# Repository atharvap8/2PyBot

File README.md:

# 2PyBot: Self-Balancing Robot

2PyBot v4.0.1 is an ESP32 self-balancing robot with two M0601 RS485 BLDC hub motors, integrated wheel feedback, and an ISM6HG256X IMU. The firmware uses **LQR/LQI state feedback** for balance and position hold. An EVOFOX One S gamepad pairs directly through Bluepad32. USB serial carries host drive commands, telemetry, and parameter tuning. See the [BLDC integration notes](docs/BLDC_V4.md) for wiring, polarity, full-stick control and turning changes.

## Current firmware

- 200 Hz control loop using pitch, pitch rate, wheel position, velocity, and position integral.
- One RS485 UART per wheel, with current control and absolute-position feedback.
- Encoder-differential heading hold and slew-limited steering.
- Normal hold, stiff hold, velocity tracking, and climb reference tracking.
- Terrain roughness, airborne, and landing detection with pitch-gain softening.
- Metadata-driven runtime parameters with bounded writes and separate BLDC NVS storage.
- Auto-tuning routines for wobble, trim, radius, and stall speed, with current limitations documented in the tuning guide.
- WS2812 status ring, camera pan/zoom servos, and PWM torch.

## Control and communication

The gamepad's left stick drives and steers. The right stick pans and zooms the camera. START requests arming; SELECT stops balancing. LB toggles LOW/HIGH speed, RB toggles the torch, and the D-pad controls hold modes and torch brightness.

Fresh host `V,<forward>,<steering>,<enable>` commands take priority over gamepad driving. `V` commands do not arm the robot. Use gamepad START or serial `E`. With no fresh input, drive commands become zero and balancing continues.

USB serial runs at **460800 baud**. The firmware emits `O` odometry and `D` debug telemetry at nominal 50 Hz, plus `HM` motor feedback at 10 Hz. Debug starts enabled; `L` toggles it. See the [serial protocol](firmware/BaseLink/PROTOCOL.md) for fields and commands.

## Repository layout

```text
firmware/
  BaseLink/                 Robot firmware and serial protocol
    BaseLink.ino            State machine, control, input arbitration
    config.h                Pins and compiled defaults
    params.h / params.cpp   Runtime parameters and NVS persistence
    autotune.h              Calibration and tuning routines
    terrain.h               Roughness, airborne, and landing detection
    bt_gamepad.h            Bluepad32 input mapping
    imu_sensor.h / .cpp      Mahony attitude estimation
    m0601.h / .cpp           RS485 framing, CRC and reply ownership
    hub_drive.h / .cpp       Two hub motors, feedback and mode handshake
    hub_control.h           Balance-priority common/turn current control
    led_ring.h / .cpp        WS2812 status display
    payload.h               Camera servos and torch
  Controller/               Legacy ESP-NOW joystick transmitter
software/
  android/                  Kotlin/Compose Android app
  radxa/
    console/                Current browser console and Android API
    deployment/             Installed services, MediaMTX, and device rules
  runtime/vision_controller/ Older collision guard and person follower
gui/                        Legacy PID desktop interface
tools/
  controller_lab/           Browser simulation lab
  tuner/                    Legacy Web Serial PID tuner
docs/                       Architecture, control theory, tuning, history
scripts/                    Model generation and Radxa utilities
hardware/cad/enclosure/rev5/ OpenSCAD enclosure source and STL exports
models/                     CAD assets
assets/                     Project media
```

## Build and first connection

1. Install the ESP32 + Bluepad32 board package and the libraries listed in the [firmware setup guide](firmware/BaseLink/README.md).
2. Select ESP32 Dev Module with the Huge APP partition scheme.
3. Open `firmware/BaseLink/BaseLink.ino`, review the pin assignments in `config.h`, and flash.
4. Open USB serial at 460800 baud with newline termination. Check the IMU and driver boot messages, then send `P?` to inspect loaded parameters.
5. Pair the EVOFOX One S in Home+A mode. Leave both sticks centered while calibration completes.
6. Use the [v4 hardware guide](docs/BLDC_V4.md) for the BLDC pin map, confirmed polarity, parameter schema and offline verification.

Saved v4 NVS parameters take precedence over compiled defaults in `2pybot-bldc4`. `PD` restores defaults in RAM; `PS` saves them with motors stopped. `ISGN` and `RPMSGN` are fixed at -1; `HUBVSRC` defaults to 1. Full-stick HIGH requests 1.00 m/s; `MAXSPD=0` leaves firmware speed uncapped. `VNOLOAD` is informational, not a driving limit.

## Host software status

| Component | Current compatibility |
| :--- | :--- |
| USB terminal or custom serial client | Supports the current parameter and telemetry protocol |
| `software/radxa/console/` | Current Radxa console: 460800 baud, live parameter metadata, browser UI, Android API, and WebRTC camera |
| `software/android/` | Kotlin/Compose client for console HTTP/WebSocket and MediaMTX WHEP; parameter groups are dynamic |
| `software/runtime/vision_controller/radxa_brain.py` | Uses `O` and `V` messages, but still has 115200 baud and 0.035 m radius constants; align both before use |
| `gui/robot_controller_ui.py` | Legacy PID UI: 115200 baud, tab-separated telemetry, and `$` commands; needs a protocol update |
| `tools/tuner/tuner.html` | Legacy Web Serial PID tuner; not a current parameter-store client |
| `firmware/Controller/Controller.ino` | Legacy ESP-NOW transmitter; current BaseLink has no ESP-NOW receiver |

The current console package was imported from the Cubie A7A. See its [setup and API guide](software/radxa/console/README.md) and [deployment layout](software/radxa/README.md). Its debug parser reads the 20 controller/terrain fields plus nine appended fall-prevention fields; a terrain parameter tab remains pending. **Driving view** shows the assembled CAD, measured VL53L5CX returns, trail and optional forward-reference guard, off by default. Live camera is available separately in that view and in Camera.

Local revision **3.9.0** adds a [predictive fall-prevention reference governor](docs/diagnostics/fall-prevention.md) with full recovery feedback and balance-priority steering allocation. Its read-only monitor is `/ui/drive-monitor.html`; a repeat physical reversal test is needed to measure fall reduction.
Local revision **3.10.0** adds [automatic load-aware climb](docs/diagnostics/auto-climb.md), gradual controller handover and a fix for mild-recovery integral washout. Automatic/manual controls are at `/ui/auto-climb.html`; the recorder includes actual climb-integral and detector state.
Current development revision **4.0.0** replaces the stepper drive with [M0601 BLDC hubs](docs/BLDC_V4.md). It retains the [adaptive Android cockpit](docs/ANDROID_COCKPIT_DESIGN.md) and [route autopilot](docs/ROUTE_AUTOPILOT.md). [Compiled-build reflashing](docs/FIRMWARE_REFLASH.md) is under **More → Setup → Controller firmware**; its tuning-restore path requires a matching hardware schema. [Camera stabilisation](docs/CAMERA_STABILISATION.md) covers the proposed pitch gimbal and isolated sensor pod.

[Boot coordination](scripts/radxa/BOOT_COORDINATION.md) holds the ESP32's USB reset until the Radxa camera, API and hotspot are ready, then releases a firmware startup interlock. A deliberate local START request is still required. [Printed mass and LQI calculations](hardware/dynamics/README.md) contain re-sliced estimates and updated estimated gains validated against geometry, filtering, latency and acceleration limits.

The older Radxa brain provides GUARD/FOLLOW modes. It owns the camera and serial port, so it cannot run alongside the console. See its [setup guide](software/runtime/vision_controller/README_RADXA.md).

The [Android app](software/android/README.md) has Drive, Live, Map, Tune, Auto, Camera, Data and Setup screens. It defaults to the Radxa hotspot address `10.42.0.1`. Drive uses a touch-navigable shaded world; Data records labelled terrain sessions; Map and Setup export reports. Its Tune screen includes all groups reported by firmware, including TERRAIN. See [terrain sessions and Drive](docs/terrain-sessions.md) for current behaviour.

## Next vision milestones

The [Objects viewer and SLAM notes](docs/ML_AND_SLAM.md) describe the lightweight
ONNX detector, temporary tracks, and the calibration/telemetry needed for later mapping.

The [guided camera calibration suite](docs/CAMERA_CALIBRATION.md) provides
target printing, automatic capture/analysis and corrected previews, with depth
health and frame timing. It is available in the console's Calibration tab and
Android Camera screen. Real target views are needed to obtain actual coefficients.

The [vision roadmap](docs/VISION_ROADMAP.md) tracks camera distortion/intrinsic
calibration, sensor extrinsics, synchronized camera/ToF distance overlays and
later ONNX detection/tracking. Camera geometric calibration is separate from
the existing colour/exposure tuning. The first proposed milestone is a measured
intrinsic calibration and validated undistorted preview.

## Revision Table

The [Revision Table](docs/REVISION_HISTORY.md) covers the main releases and
features, along with estimated dates for upcoming work. Smaller fixes are grouped
together. See the [vision roadmap](docs/VISION_ROADMAP.md) for the detailed task list.

## Updating the bot

See the [one-pull development SOP](docs/DEVELOPMENT_SOP.md) for coordinated Git
pulls, versioned host releases, firmware updates and deployment LED states.

The managed source checkout is `/home/radxa/projects/2PyBot`; the console runs from a versioned release snapshot. After one-time setup, `git pull --ff-only` waits for coordinated deployment and reports its outcome. Firmware updates use the existing application-only flash worker when their inputs change. CAD/documentation-only updates leave running services untouched. See the SOP for setup, status and recovery, or [repo-based deployment](scripts/radxa/README.md) for legacy installations.

## Hardware defaults

| Component | Configuration |
| :--- | :--- |
| Robot controller | ESP32 DevKit |
| Wheel drive | Two M0601 BLDC hubs, independent RS485 UARTs, current mode |
| Wheel feedback | Integrated absolute position; internal 4096-count/revolution units |
| Wheel radius | 0.052 m compiled default |
| Attitude | ISM6HG256X accelerometer/gyro, Mahony filter |
| Compass | QMC5883L, tilt-compensated yaw telemetry |
| Gamepad | EVOFOX One S through Bluepad32 |
| Status ring | 16 WS2812 LEDs on GPIO 15 |
| Camera payload | MG90S pan/zoom servos on GPIO 26/0; torch on GPIO 2 |

## Enclosure CAD

[Revision 5](hardware/cad/enclosure/rev5/README.md) includes the base tray, shell, face plate, and left/right motor covers as OpenSCAD source and five STL exports. The enclosure is **not yet printed or physically fit-tested**. Estimated dimensions are marked in the source. The imported face STL has three zero-area triangles that need re-export or repair before printing.

The existing simplified STEP model remains in `models/2pybot_simplified.step`; it is separate from the revision-5 enclosure package.

## Documentation

| Document | Contents |
| :--- | :--- |
| [Firmware setup](firmware/BaseLink/README.md) | Build, wiring, pairing, controls |
| [Serial protocol](firmware/BaseLink/PROTOCOL.md) | Commands, parameter records, telemetry fields |
| [Radxa console](software/radxa/console/README.md) | Browser UI, Android API, camera pipeline, deployment |
| [Lidar mapping](docs/LIDAR_SLAM.md) | RPLIDAR C1 wiring, standalone SLAM page, first use |
| [Android app](software/android/README.md) | Build, host connection, screens, parameter and video transport |
| [Vision roadmap](docs/VISION_ROADMAP.md) | Planned lens calibration, sensor geometry, depth fusion and ONNX perception |
| [Camera calibration](docs/CAMERA_CALIBRATION.md) | Guided capture, lens fitting, reports, depth health and frame timing |
| [Terrain sessions and Drive](docs/terrain-sessions.md) | Recording, 3D world coordinates, guard and range calibration |
| [Radxa deployment](scripts/radxa/README.md) | Git updates, selective restarts, systemd timer, health checks |
| [Enclosure CAD](hardware/cad/enclosure/rev5/README.md) | Revision-5 source, exports, dimensions, and current print status |
| [System architecture](docs/BaseLink/System_Architecture.md) | Sensors, control, actuation, host links |
| [LQR/LQI theory](docs/BaseLink/PID_Theory_and_Math.md) | State feedback, control modes, filtering, limits |
| [Configuration and tuning](docs/BaseLink/Config_and_Tuning_Guide.md) | Defaults, runtime settings, calibration |
| [Program flow](docs/BaseLink/Program_Flow_State_Machine.md) | Boot sequence and state transitions |
| [Troubleshooting](docs/BaseLink/Troubleshooting_Guide.md) | Common faults and source-level checks |
| [Detailed reference](docs/BaseLink/100+_WHAT_AND_HOWS.md) | 126 code-mapped checks |
| [TMC2226 migration](docs/BaseLink/TMC2226_Migration.md) | Driver configuration and migration history |
| [Project history](docs/BaseLink/Project_History.md) | PID, ESP-NOW, LQR/LQI, and runtime-tuning milestones |
| [Legacy transmitter](docs/Controller/System_Architecture.md) | ESP-NOW joystick packet and sampling |

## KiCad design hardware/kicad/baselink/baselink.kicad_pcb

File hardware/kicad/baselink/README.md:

# BaseLink controller board (KiCad 10)

STM32G474RET6 balance controller for 2PyBot: ELRS radio (CRSF), two RS485
hub-motor links, Radxa Cubie host header, 5S battery input with ideal-diode
reverse protection and current monitor, an LM5069 hot-swap motor bus switch
driven by a hardware safety chain (motor watchdog AND E-stop), three
independent 5 V rails and a 3V3 LDO. Architecture: see the conversation
notes / `docs` (STM32 + ELRS plan).

**Status: schematic draft r0.1 + placeholder PCB.** Footprints are placed
automatically in one region per block; nothing is routed. Verify the STM32 pin
map in STM32CubeMX, the Cubie A7A 40-pin mapping, the ISM6HG256X pinout
(ISM330DHCX symbol used) and the hot-swap/UVLO values before layout.

## Files

| File | What |
|---|---|
| `baselink.kicad_pro` | Project: net classes (Default, Battery, Rail5V, RS485), 4-layer rules |
| `baselink.kicad_sch` | Root: block diagram of the hierarchical sheets |
| `power_input`, `motor_power`, `regulators`, `mcu`, `rs485`, `comms`, `io` `.kicad_sch` | One sheet per block |
| `baselink.kicad_pcb` | Placeholder board: all 144 footprints, nets, outline, M3 holes, GND plane on In1 |
| `baselink.kicad_sym`, `sym-lib-table` | Project power symbols (VBAT, VMOT, +5V_SBC, +5V_ACT, +5V_CTRL, +3V3A) |
| `build/baselink_schematic.pdf` | Schematic PDF |
| `build/erc.rpt`, `build/drc.rpt` | Last check results |
| `tools/design.py` | **The circuit**: every part, footprint and pin-to-net map |
| `tools/gen_sch.py` | Generates the project, symbol library and all sheets |
| `tools/gen_pcb.py` | Generates the board with KiCad's Python (pcbnew) |

## Regenerate

```powershell
cd hardware\kicad\baselink
python tools\gen_sch.py                                  # project + schematic + build\netlist.json
D:\7_Tools\KiCad\bin\python.exe tools\gen_pcb.py         # placeholder board
D:\7_Tools\KiCad\bin\kicad-cli.exe sch erc baselink.kicad_sch -o build\erc.rpt --severity-all
D:\7_Tools\KiCad\bin\kicad-cli.exe pcb drc baselink.kicad_pcb -o build\drc.rpt --severity-all
D:\7_Tools\KiCad\bin\kicad-cli.exe sch export pdf baselink.kicad_sch -o build\baselink_schematic.pdf
```

Edit `tools/design.py`, not the generated `.kicad_sch` files. `gen_sch.py`
checks every pin name against the library symbol and every pin number against
the footprint's pads, and lists unconnected pins.

**Once layout starts, stop regenerating the board.** Edit the schematic source
and use *Tools → Update PCB from Schematic* in KiCad; footprints carry their
schematic links, so placement and routing are kept.

## Known check results

- ERC: 1 warning. IMU `SDx` is tied to GND as the datasheet recommends for an
  unused aux bus; it is bidirectional, so ERC flags it against the GND flag.
- DRC: only unrouted connections and library silkscreen overlaps.

## Sheets

| Sheet | Contents |
|---|---|
| Power input | XT60, 30 A blade fuse, LM74700 + N-FET ideal diode, SMDJ26A, bulk, 1 mΩ shunt + INA228, VBAT ADC divider |
| Motor switch | LM5069 hot-swap + N-FET + 2 mΩ sense, fail-safe UVLO enable (BSS138 + BSS84), 74LVC1G123 motor watchdog, 74LVC1G08 AND with the E-stop loop, VMOT TVS + bulk, 2× XT30 |
| Regulators | 3× Pololu D36V step-down placeholders (+5V_SBC 5 A, +5V_ACT 3 A, +5V_CTRL 0.6 A), TLV75733 3V3 LDO, power LED |
| MCU | STM32G474RET6 LQFP64, decoupling, VDDA ferrite, 24 MHz crystal, BOOT0/NRST, buttons, 10-pin SWD, USB-C with USBLC6 and VBUS OR-ing, status LED |
| RS485 | 2× socketed DIP-8 transceivers (SN65HVD3082E class), termination jumpers, DNP bias, SM712, JST-GH |
| Comms | ELRS JST-GH, Radxa 2×20 socket (5 V, host UART, BOOT0/NRST via 1 k, lidar and ToF pass-through), SN65HVD230 CAN, spare UART |
| IO | IMU (SPI + 2 INT), 2× Qwiic, WS2812 level shifter + connector, 4 servo headers, torch MOSFET, buzzer driver, rail and NTC ADC dividers |

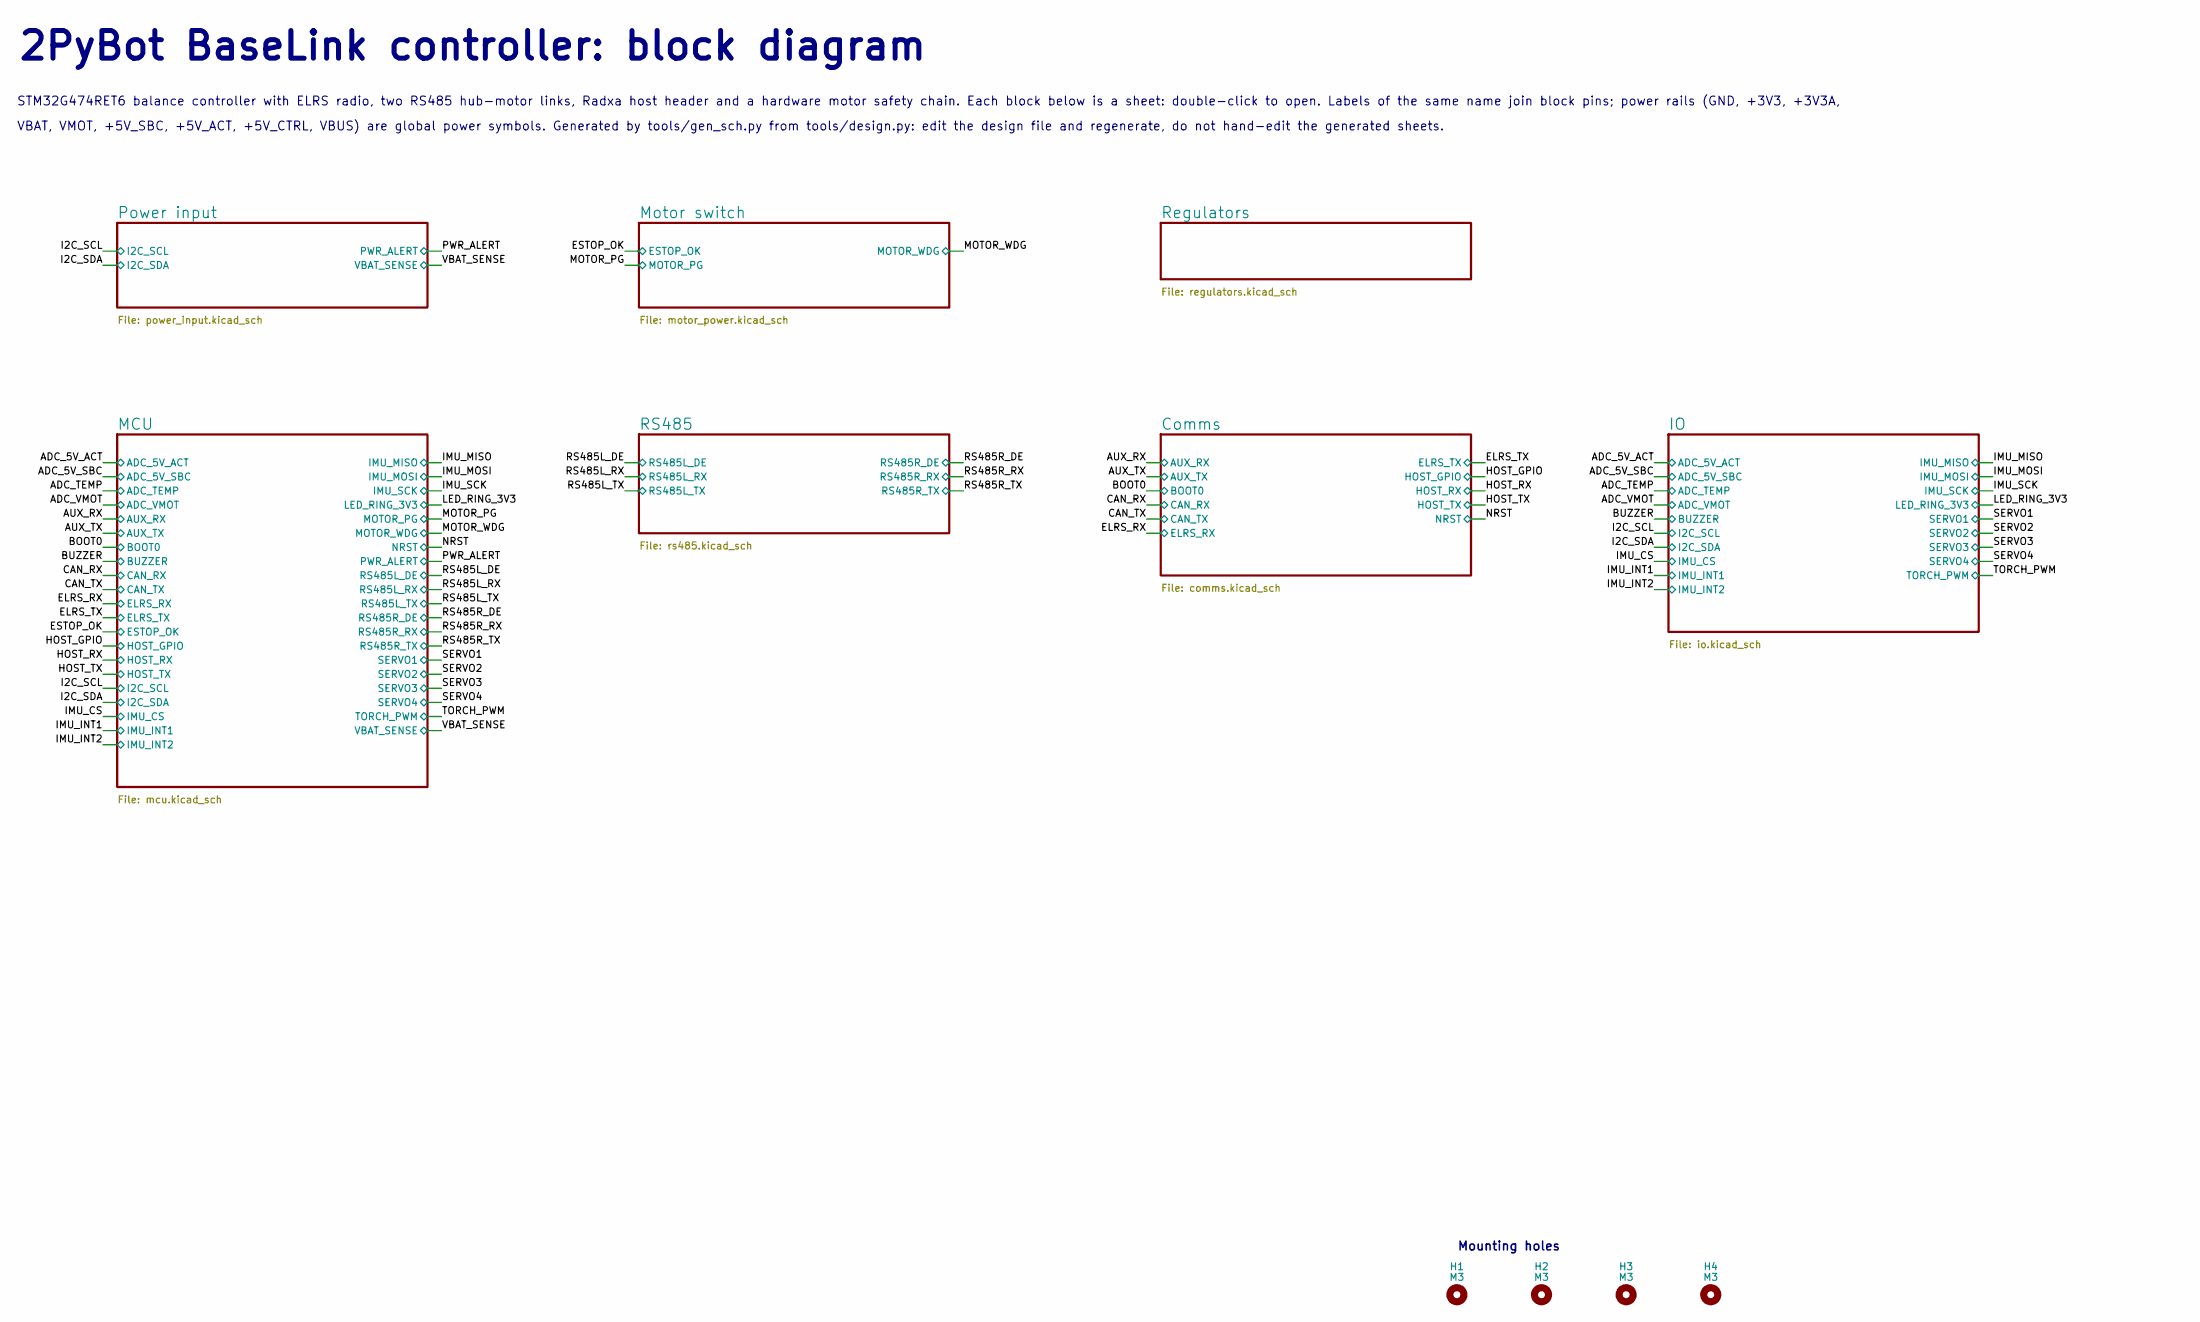
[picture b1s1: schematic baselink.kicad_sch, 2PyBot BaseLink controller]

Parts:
H1, H2, H3, H4: M3; MountingHole_3.2mm_M3

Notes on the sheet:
2PyBot BaseLink controller: block diagram
STM32G474RET6 balance controller with ELRS radio, two RS485 hub-motor links, Radxa host header and a hardware motor safety chain. Each block below is a sheet: double-click to open. Labels of the same name join block pins; power rails (GND, +3V3, +3V3A,
VBAT, VMOT, +5V_SBC, +5V_ACT, +5V_CTRL, VBUS) are global power symbols. Generated by tools/gen_sch.py from tools/design.py: edit the design file and regenerate, do not hand-edit the generated sheets.
Mounting holes

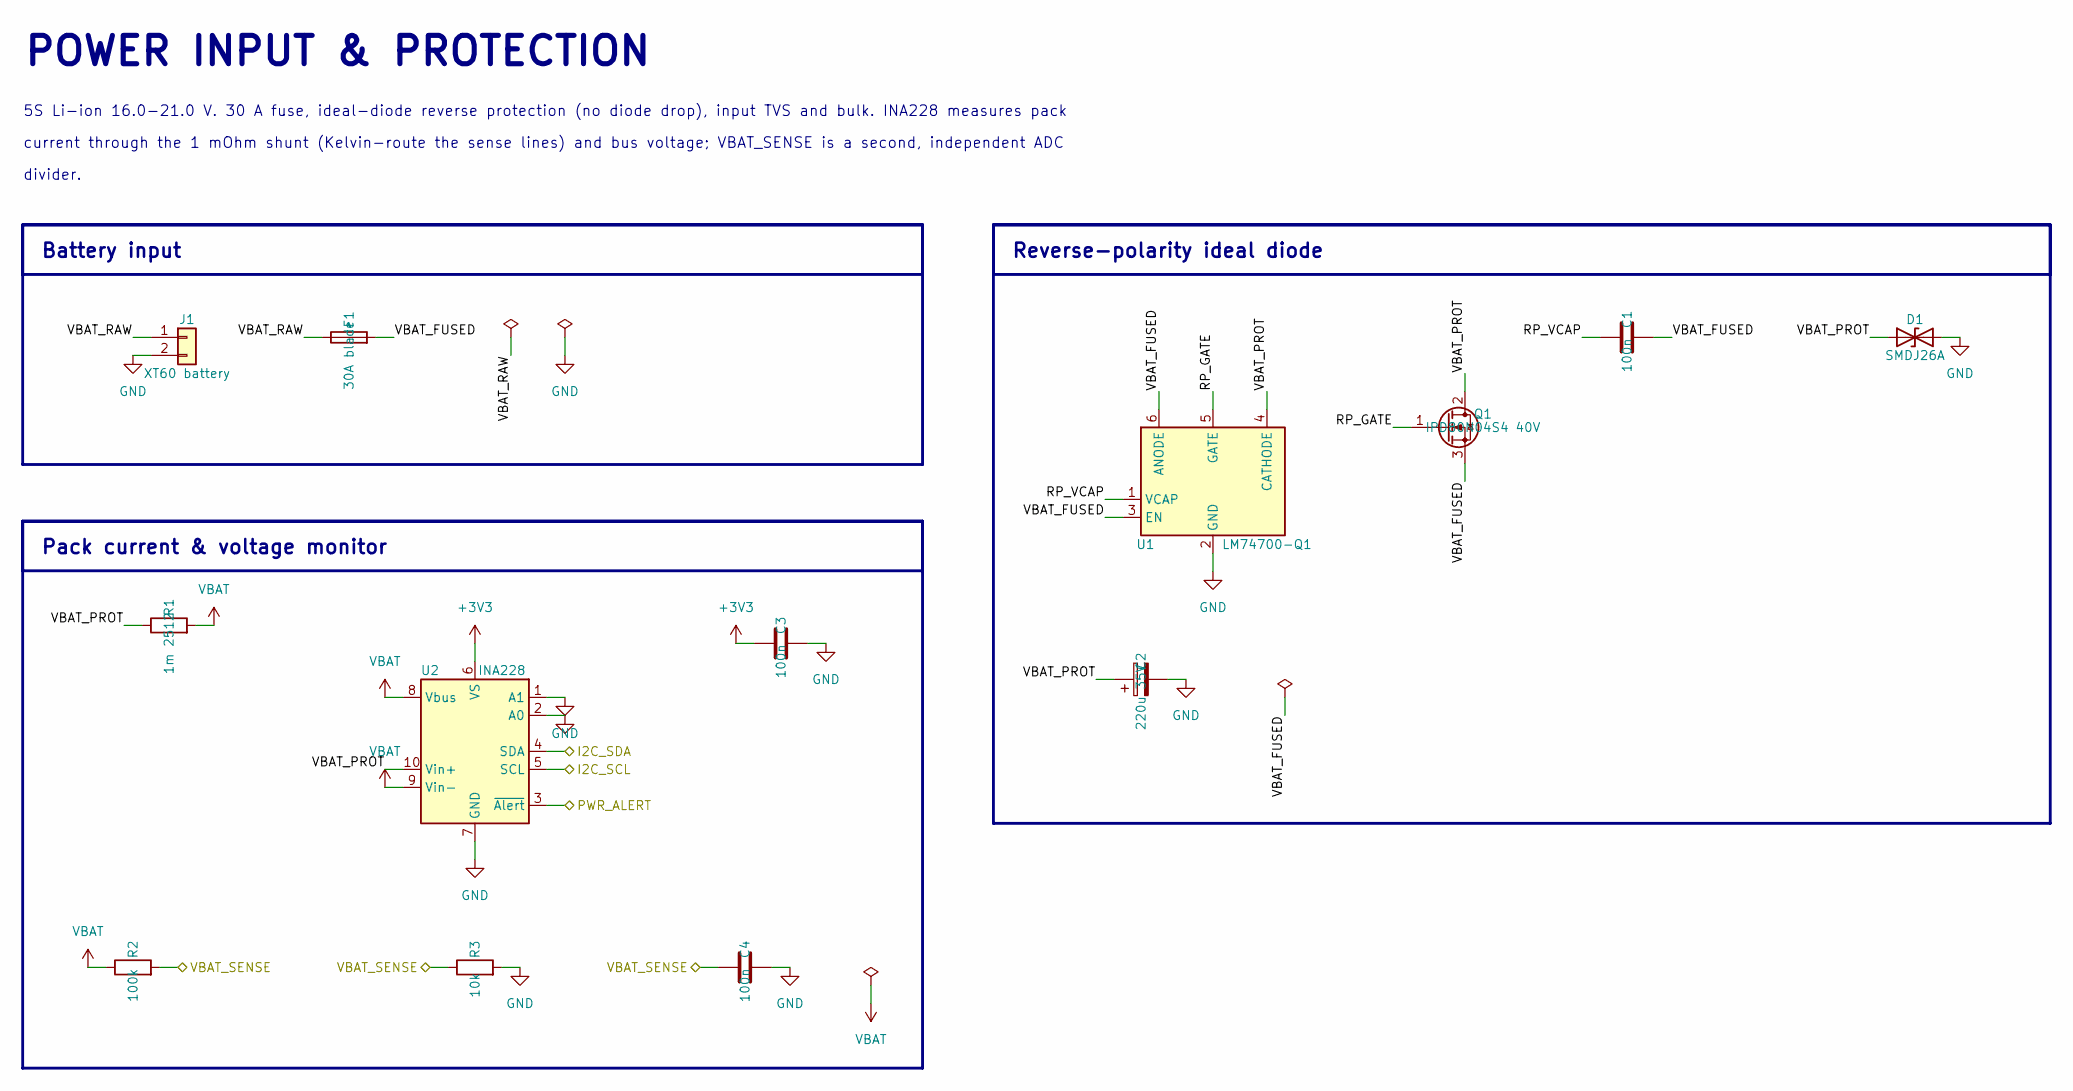
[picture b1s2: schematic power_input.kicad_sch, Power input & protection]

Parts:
C1, C3, C4: 100n; C_0603_1608Metric
C2: 220u 35V; CP_Elec_10x10
D1: SMDJ26A; D_SMC
F1: 30A blade; Fuseholder_Blade_Mini_Keystone_3568
J1: XT60 battery; AMASS_XT60PW-M_1x02_P7.20mm_Horizontal
Q1: IPD80N04S4 40V; TO-252-2
R1: 1m 2512; R_2512_6332Metric
R2: 100k; R_0603_1608Metric
R3: 10k; R_0603_1608Metric
U1: LM74700-Q1; SOT-23-6
U2: INA228; TSSOP-10_3x3mm_P0.5mm

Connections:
+3V3: C3.1, U2.6 (VS); also elsewhere on the board
/I2C_SCL: U2.5 (SCL); also elsewhere on the board
/I2C_SDA: U2.4 (SDA); also elsewhere on the board
/PWR_ALERT: U2.3 (~Alert); also elsewhere on the board
/Power input/RP_GATE: Q1.1 (G), U1.5 (GATE)
/Power input/RP_VCAP: C1.1, U1.1 (VCAP)
/Power input/VBAT_FUSED: C1.2, F1.2, Q1.3 (S), U1.3 (EN), U1.6 (ANODE)
/Power input/VBAT_PROT: C2.1, D1.1 (A1), Q1.2 (D), R1.1, U1.4 (CATHODE), U2.10 (Vin+)
/Power input/VBAT_RAW: F1.1, J1.1
/VBAT_SENSE: C4.1, R2.2, R3.1; also elsewhere on the board
GND: C2.2, C3.2, C4.2, D1.2 (A2), J1.2, R3.2, U1.2 (GND), U2.1 (A1), U2.2 (A0), U2.7 (GND); also elsewhere on the board
VBAT: R1.2, R2.1, U2.8 (Vbus), U2.9 (Vin-); also elsewhere on the board

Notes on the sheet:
POWER INPUT & PROTECTION
5S Li-ion 16.0-21.0 V. 30 A fuse, ideal-diode reverse protection (no diode drop), input TVS and bulk. INA228 measures pack
current through the 1 mOhm shunt (Kelvin-route the sense lines) and bus voltage; VBAT_SENSE is a second, independent ADC
divider.
Battery input
Reverse-polarity ideal diode
Pack current & voltage monitor

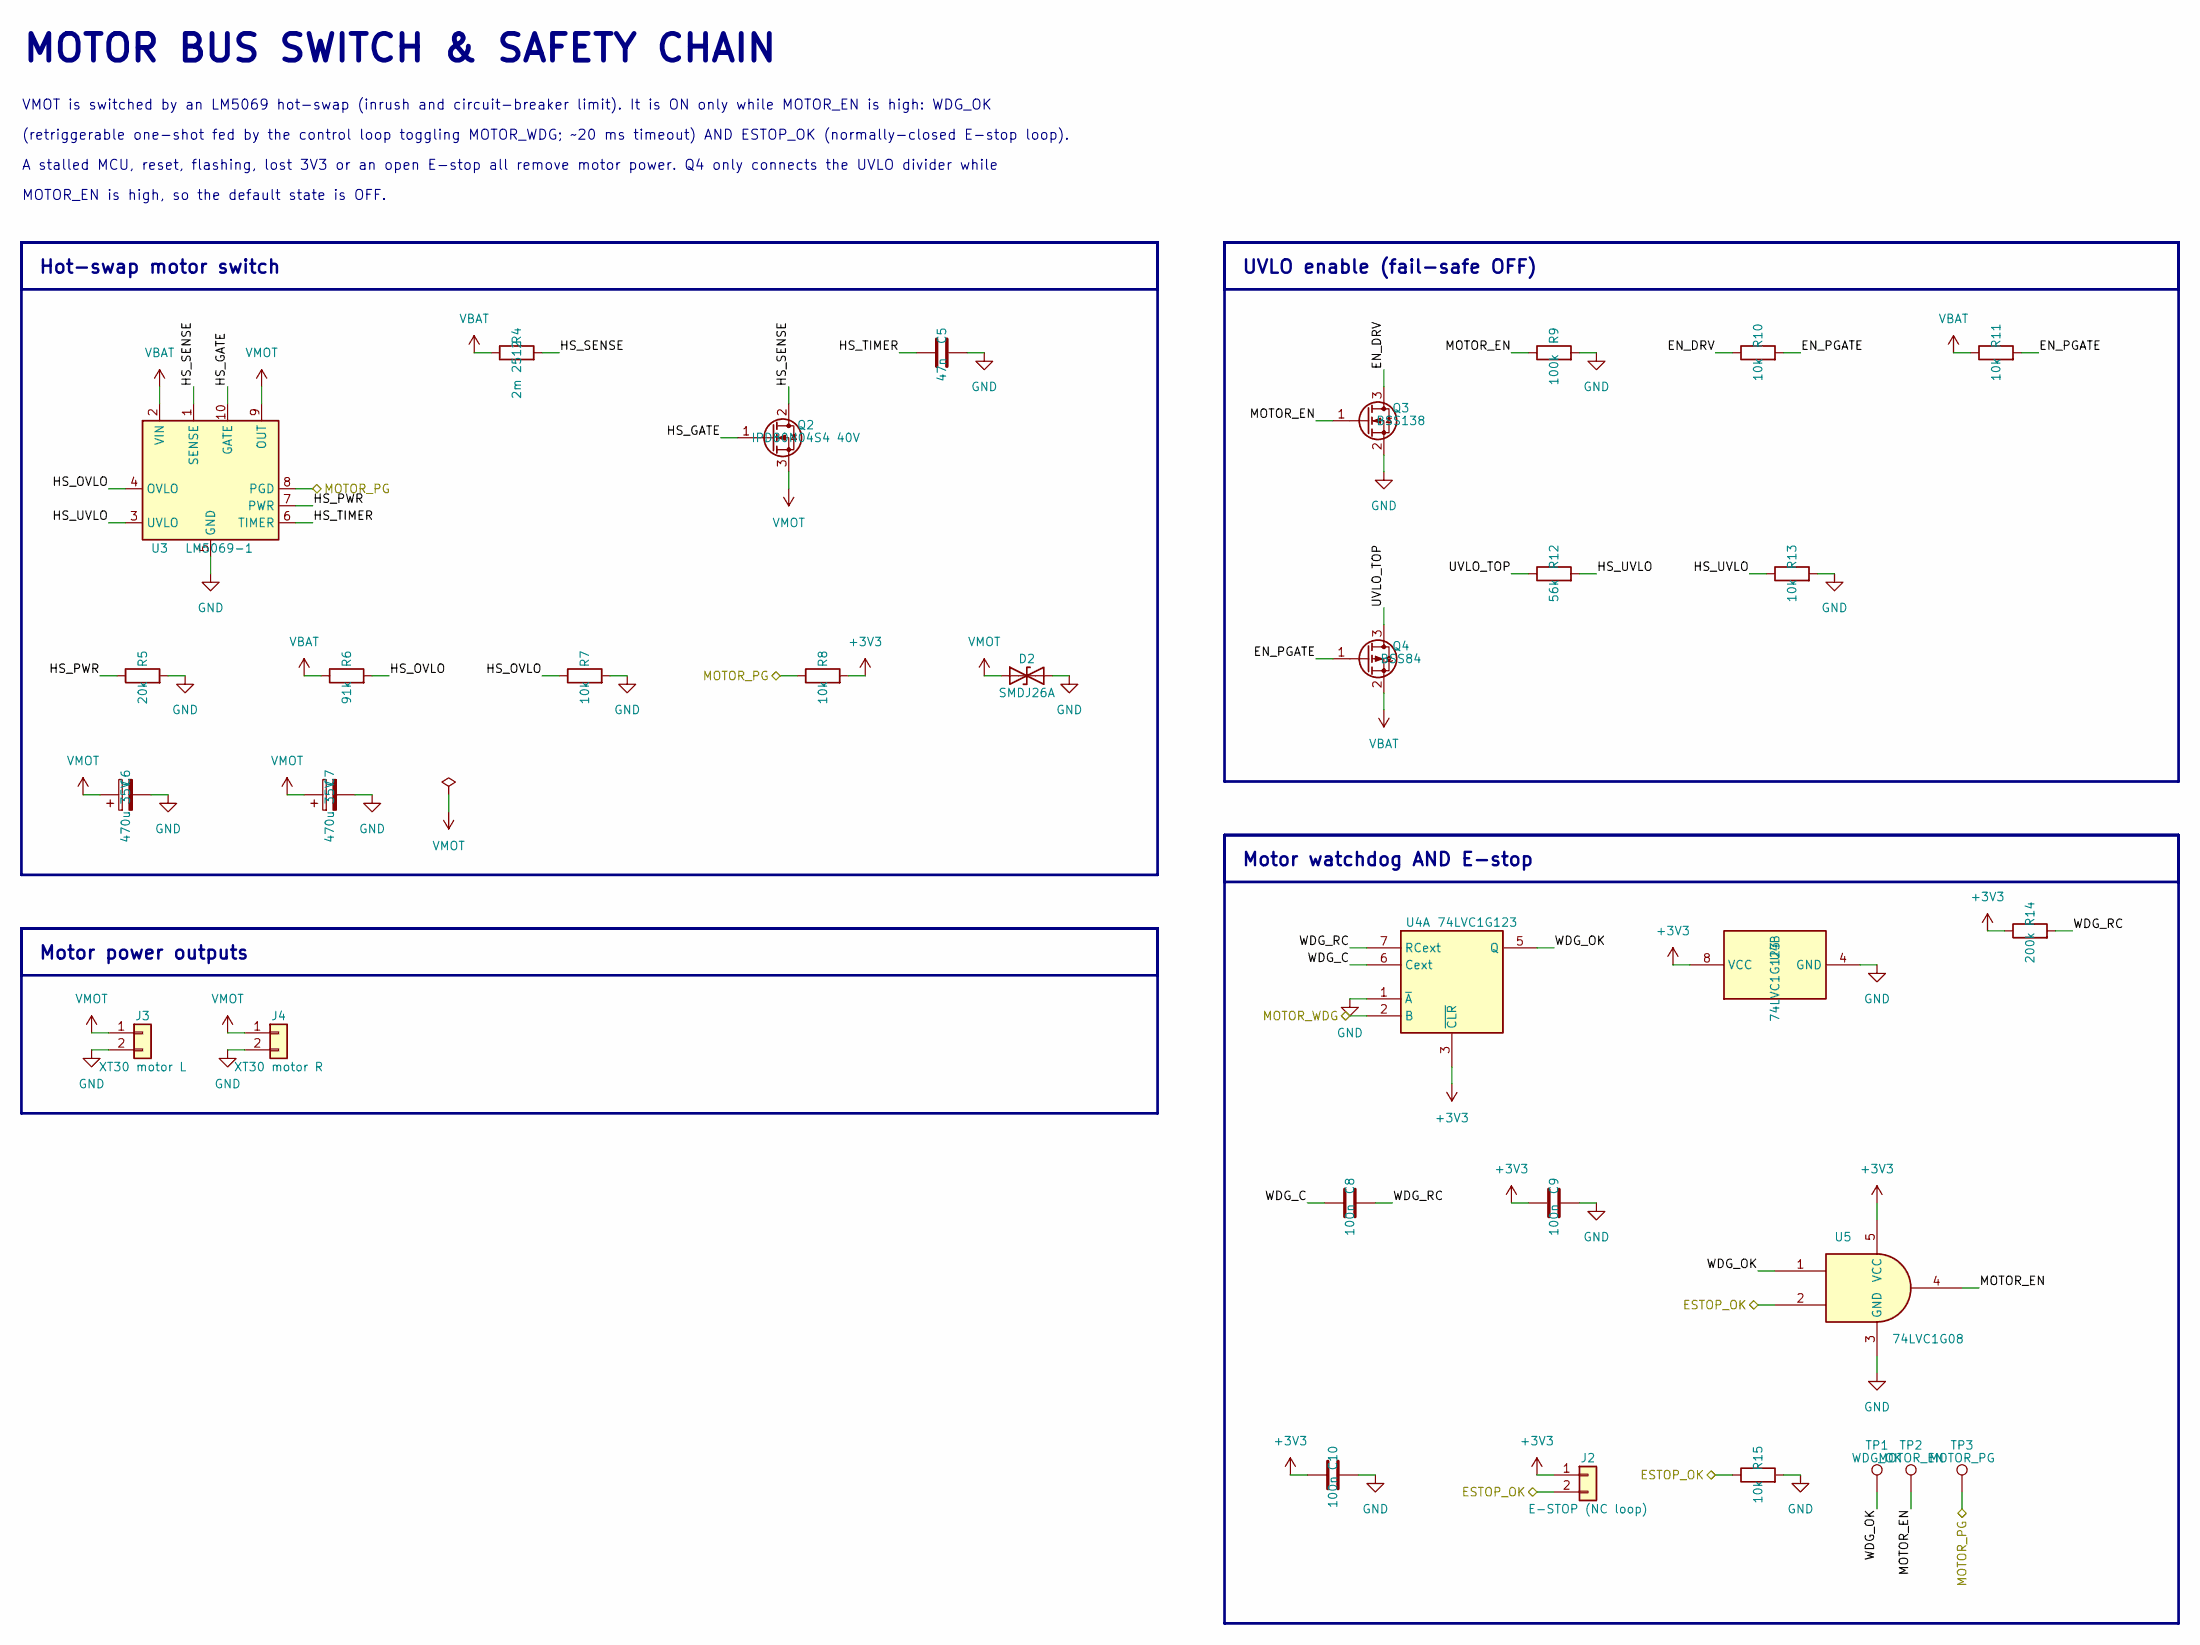
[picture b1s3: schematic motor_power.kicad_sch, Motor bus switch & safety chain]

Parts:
C5: 47n; C_0603_1608Metric
C6, C7: 470u 35V; CP_Elec_10x10
C8, C9, C10: 100n; C_0603_1608Metric
D2: SMDJ26A; D_SMC
J2: E-STOP (NC loop); PinHeader_1x02_P2.54mm_Vertical
J3: XT30 motor L; AMASS_XT30PW-M_1x02_P2.50mm_Horizontal
J4: XT30 motor R; AMASS_XT30PW-M_1x02_P2.50mm_Horizontal
Q2: IPD80N04S4 40V; TO-252-2
Q3: BSS138; SOT-23
Q4: BSS84; SOT-23
R4: 2m 2512; R_2512_6332Metric
R5: 20k; R_0603_1608Metric
R6: 91k; R_0603_1608Metric
R7, R8, R10, R11, R13, R15: 10k; R_0603_1608Metric
R9: 100k; R_0603_1608Metric
R12: 56k; R_0603_1608Metric
R14: 200k; R_0603_1608Metric
TP1: WDG_OK; TestPoint_Pad_D1.5mm
TP2: MOTOR_EN; TestPoint_Pad_D1.5mm
TP3: MOTOR_PG; TestPoint_Pad_D1.5mm
U3: LM5069-1; MSOP-10_3x3mm_P0.5mm
U4: 74LVC1G123; VSSOP-8_2.3x2mm_P0.5mm
U5: 74LVC1G08; SOT-23-5

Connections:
+3V3: C9.1, C10.1, J2.1, R8.2, R14.1, U4.3 (~CLR), U4.8 (VCC), U5.5 (VCC); also elsewhere on the board
/ESTOP_OK: J2.2, R15.1, U5.2; also elsewhere on the board
/MOTOR_PG: R8.1, TP3.1, U3.8 (PGD); also elsewhere on the board
/MOTOR_WDG: U4.2 (B); also elsewhere on the board
/Motor switch/EN_DRV: Q3.3 (D), R10.1
/Motor switch/EN_PGATE: Q4.1 (G), R10.2, R11.2
/Motor switch/HS_GATE: Q2.1 (G), U3.10 (GATE)
/Motor switch/HS_OVLO: R6.2, R7.1, U3.4 (OVLO)
/Motor switch/HS_PWR: R5.1, U3.7 (PWR)
/Motor switch/HS_SENSE: Q2.2 (D), R4.2, U3.1 (SENSE)
/Motor switch/HS_TIMER: C5.1, U3.6 (TIMER)
/Motor switch/HS_UVLO: R12.2, R13.1, U3.3 (UVLO)
/Motor switch/MOTOR_EN: Q3.1 (G), R9.1, TP2.1, U5.4
/Motor switch/UVLO_TOP: Q4.3 (D), R12.1
/Motor switch/WDG_C: C8.1, U4.6 (Cext)
/Motor switch/WDG_OK: TP1.1, U4.5 (Q), U5.1
/Motor switch/WDG_RC: C8.2, R14.2, U4.7 (RCext)
GND: C5.2, C6.2, C7.2, C9.2, C10.2, D2.2 (A2), J3.2, J4.2, Q3.2 (S), R5.2, R7.2, R9.2, R13.2, R15.2, U3.5 (GND), U4.1 (~A), U4.4 (GND), U5.3 (GND); also elsewhere on the board
VBAT: Q4.2 (S), R4.1, R6.1, R11.1, U3.2 (VIN); also elsewhere on the board
VMOT: C6.1, C7.1, D2.1 (A1), J3.1, J4.1, Q2.3 (S), U3.9 (OUT); also elsewhere on the board

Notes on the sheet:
MOTOR BUS SWITCH & SAFETY CHAIN
VMOT is switched by an LM5069 hot-swap (inrush and circuit-breaker limit). It is ON only while MOTOR_EN is high: WDG_OK
(retriggerable one-shot fed by the control loop toggling MOTOR_WDG; ~20 ms timeout) AND ESTOP_OK (normally-closed E-stop loop).
A stalled MCU, reset, flashing, lost 3V3 or an open E-stop all remove motor power. Q4 only connects the UVLO divider while
MOTOR_EN is high, so the default state is OFF.
Hot-swap motor switch
UVLO enable (fail-safe OFF)
Motor watchdog AND E-stop
Motor power outputs

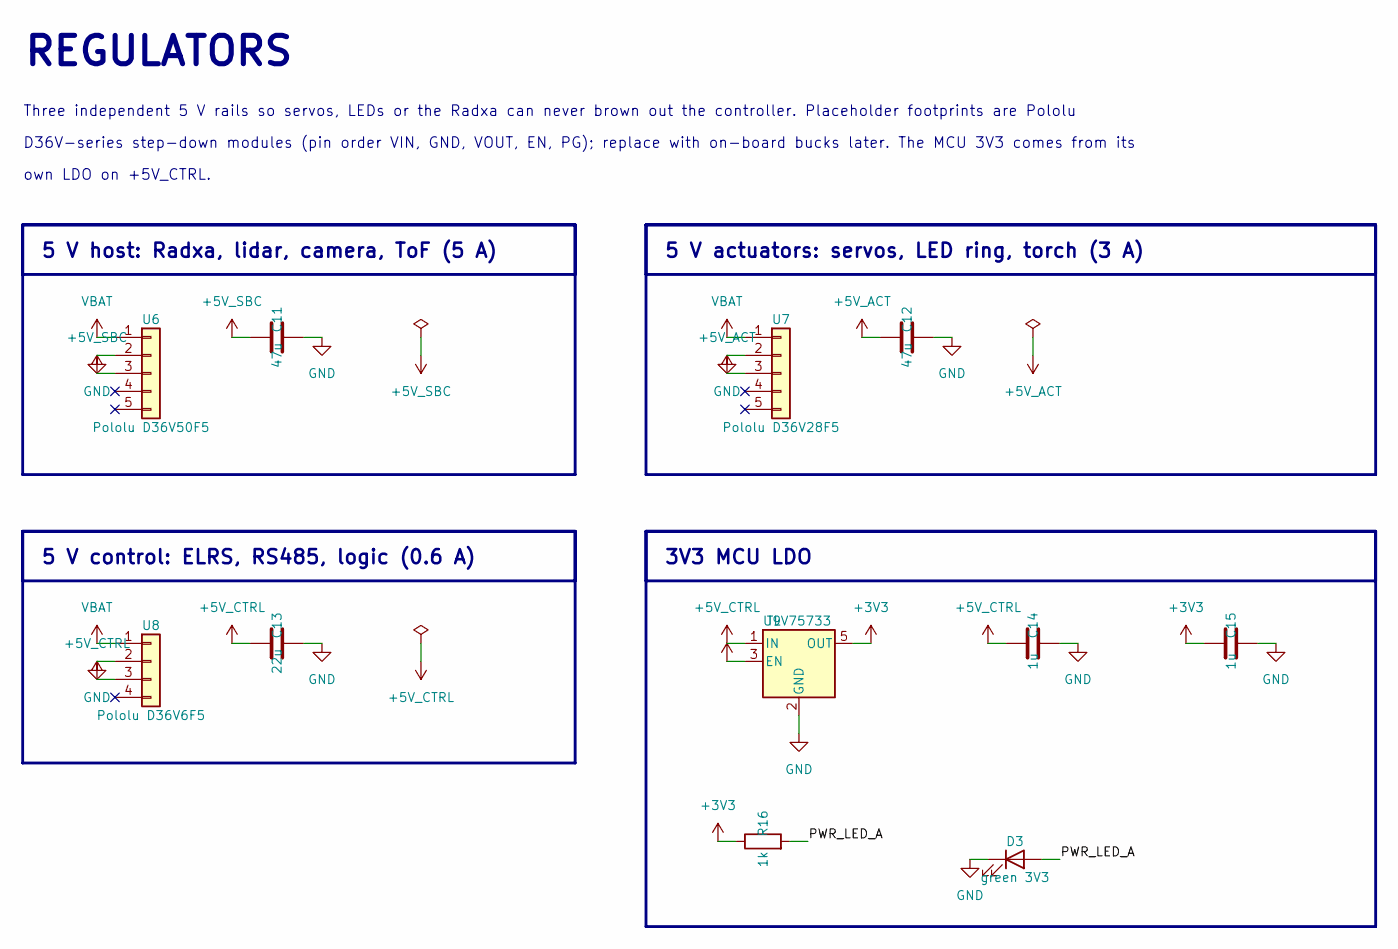
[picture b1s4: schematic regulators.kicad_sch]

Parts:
C11, C12: 47u; C_1206_3216Metric
C13: 22u; C_1206_3216Metric
C14, C15: 1u; C_0603_1608Metric
D3: green 3V3; LED_0603_1608Metric
R16: 1k; R_0603_1608Metric
U6: Pololu D36V50F5; PinHeader_1x05_P2.54mm_Vertical
U7: Pololu D36V28F5; PinHeader_1x05_P2.54mm_Vertical
U8: Pololu D36V6F5; PinHeader_1x04_P2.54mm_Vertical
U9: TLV75733; SOT-23-5

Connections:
+3V3: C15.1, R16.1, U9.5 (OUT); also elsewhere on the board
+5V_ACT: C12.1, U7.3; also elsewhere on the board
+5V_CTRL: C13.1, C14.1, U8.3, U9.1 (IN), U9.3 (EN); also elsewhere on the board
+5V_SBC: C11.1, U6.3; also elsewhere on the board
/Regulators/PWR_LED_A: D3.2 (A), R16.2
GND: C11.2, C12.2, C13.2, C14.2, C15.2, D3.1 (K), U6.2, U7.2, U8.2, U9.2 (GND); also elsewhere on the board
VBAT: U6.1, U7.1, U8.1; also elsewhere on the board

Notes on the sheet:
REGULATORS
Three independent 5 V rails so servos, LEDs or the Radxa can never brown out the controller. Placeholder footprints are Pololu
D36V-series step-down modules (pin order VIN, GND, VOUT, EN, PG); replace with on-board bucks later. The MCU 3V3 comes from its
own LDO on +5V_CTRL.
5 V host: Radxa, lidar, camera, ToF (5 A)
5 V actuators: servos, LED ring, torch (3 A)
5 V control: ELRS, RS485, logic (0.6 A)
3V3 MCU LDO
